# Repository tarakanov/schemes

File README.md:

schemes
=======

Just some schemes

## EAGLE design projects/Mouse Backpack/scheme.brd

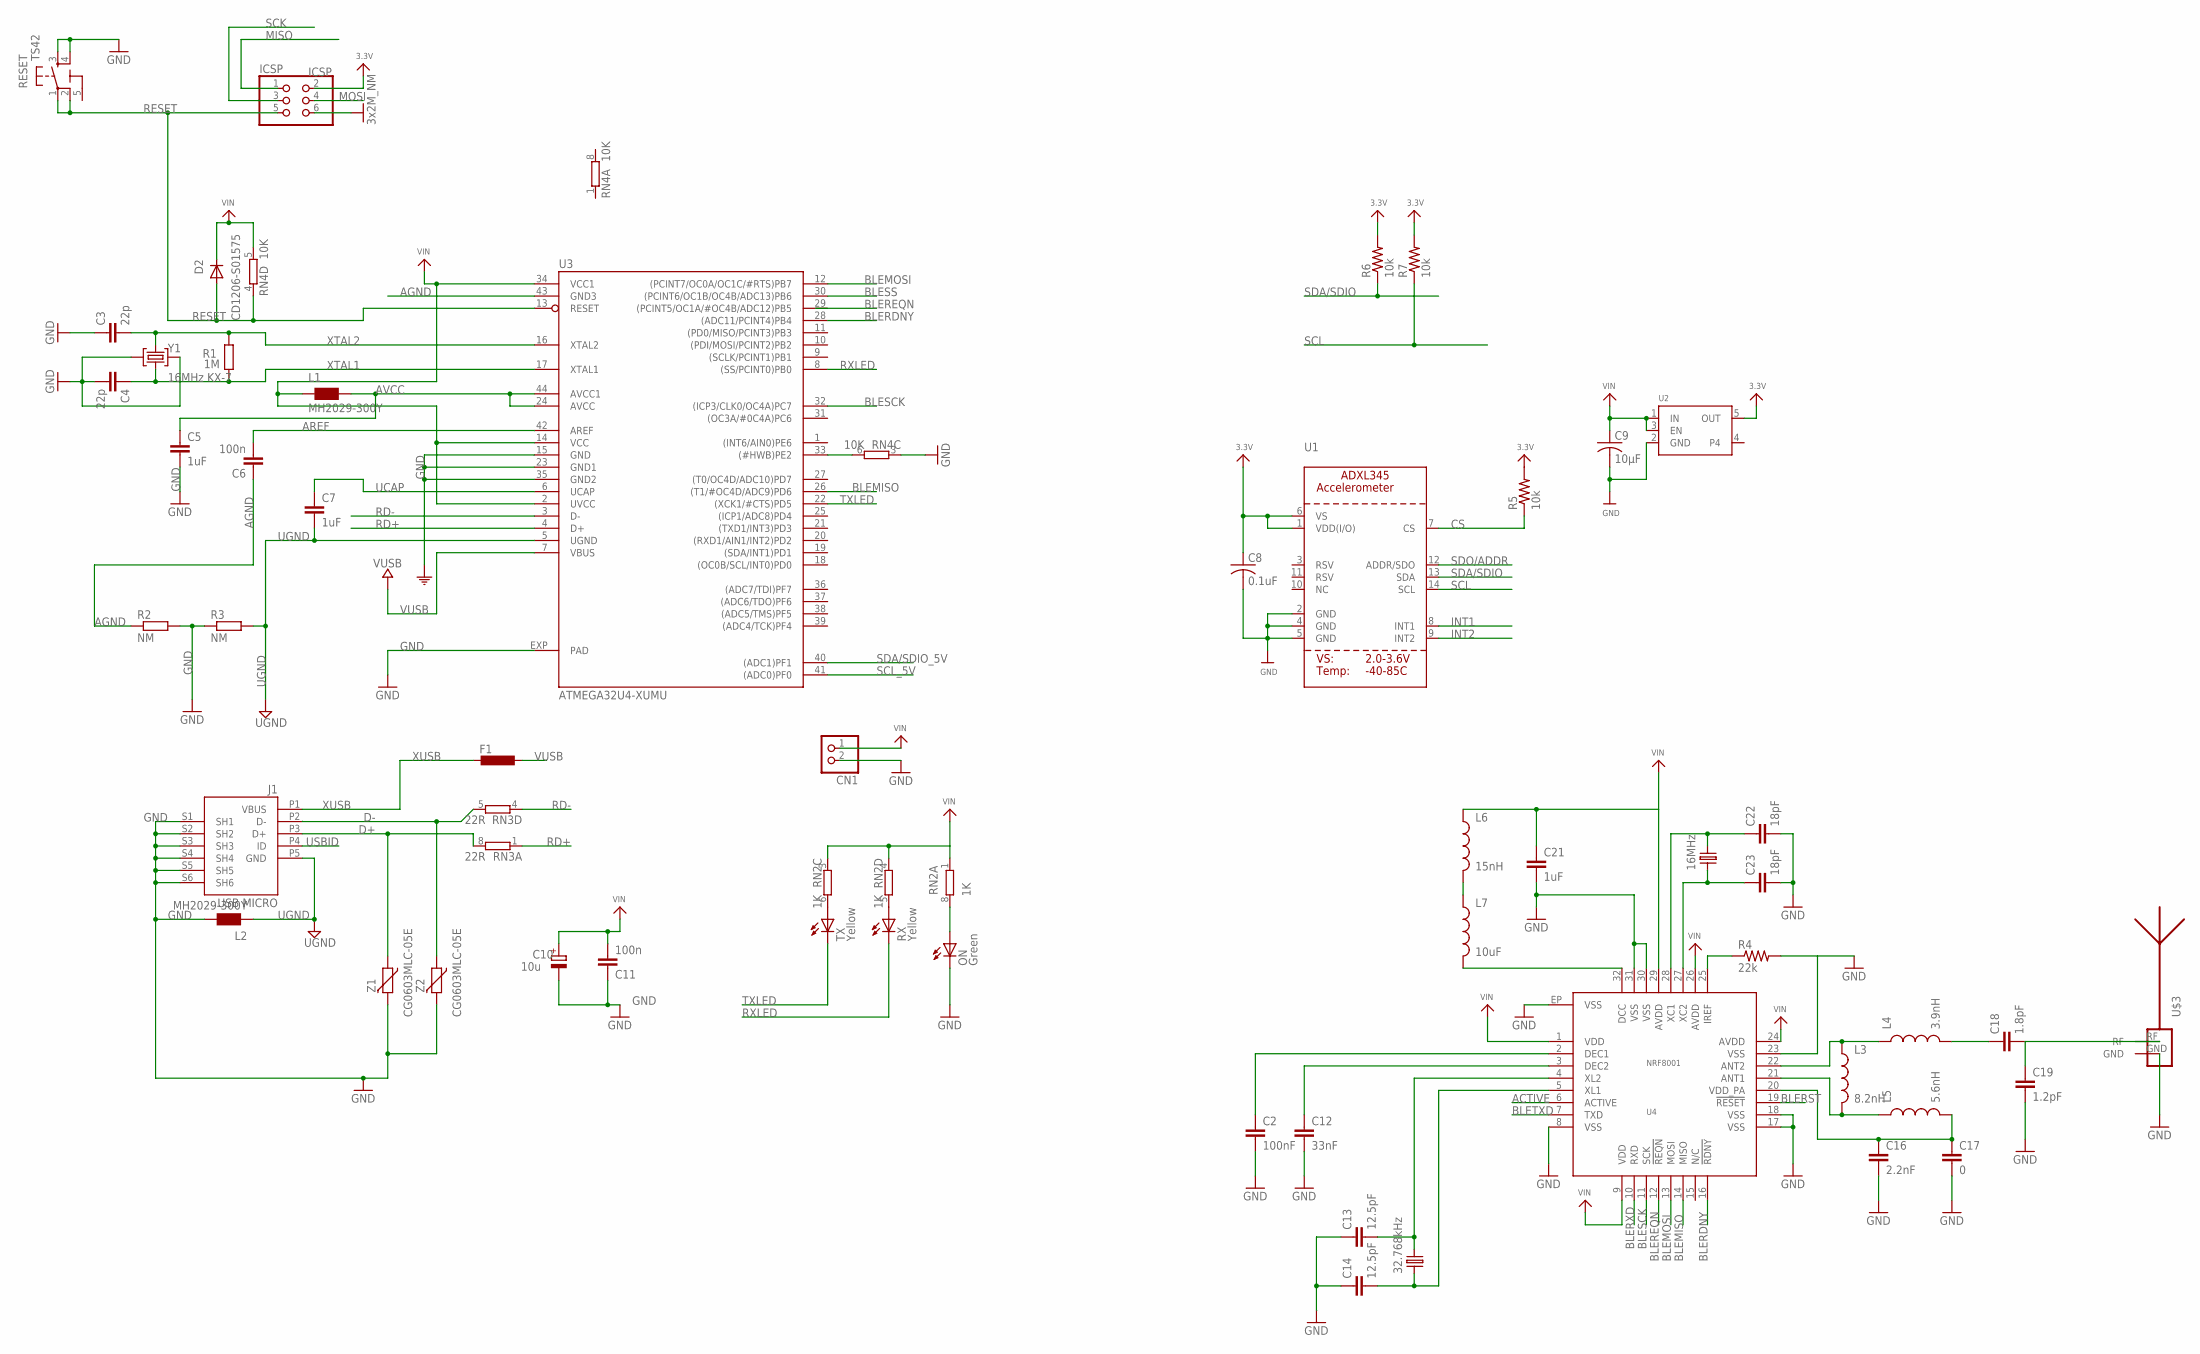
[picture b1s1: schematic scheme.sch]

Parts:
C2: 100nF; 0603-CAP
C3, C4: 22p; C0603-ROUND
C5, C7: 1uF; C0603-ROUND
C6, C11: 100n; C0603-ROUND
C8: 0.1uF; C0805
C9: 10µF; C0805
C10: 10u; SMC_B
C12: 33nF; 0603-CAP
C13, C14: 12.5pF; 0603-CAP
C16: 2.2nF; 0603-CAP
C17: 0; 0603-CAP
C18: 1.8pF; 0603-CAP
C19: 1.2pF; 0603-CAP
C21: 1uF; 0603-CAP
C22, C23: 18pF; 0603-CAP
CN1: JST_2PIN-SMT-RA; JST-PH-2-SMT-RA
D2: CD1206-S01575; MINIMELF
F1: MF-MSMF050-2 500mA; L1812
ICSP: ICSP; 2X03
J1: USB MICRO; CON2_USB_MICRO_B_AT
L1, L2: MH2029-300Y; 0805
L3: 8.2nH; 0603
L4: 3.9nH; 0603
L5: 5.6nH; 0603
L6: 15nH; 0603
L7: 10uF; 0603
ON: Green; CHIPLED_0805
R1: 1M; R0603-ROUND
R2, R3: NM; R0402
R4: 22k; 0603-RES
R5, R6, R7: 10k; 0603-RES
RESET: TS42
RN2: 1K; CAY16
RN3: 22R; CAY16
RN4: 10K; CAY16
RX: Yellow; CHIPLED_0805
TX: Yellow; CHIPLED_0805
U1: ACCEL_ADXL345; LGA14
U2: VREG_SOT23-5; SOT23-5
U3: ATMEGA32U4-XUMU; QFN44ML7X7
U4: NRF8001; QFN-32
U$3: ANTENNA_1LEFT; SWRA117D_LEFT
X1: 16MHz; CRYSTAL-2.5X3.5
X2: 32.768kHz; CRYSTAL-ABS10
Y1: 16MHz KX-7; CRYSTAL-3.2-2.5
Z1, Z2: CG0603MLC-05E; CT/CN0603

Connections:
3.3V: C8.1, ICSP.2, R5.2, R6.2, R7.2, U1.1 (VDD(I/O)), U1.6 (VS), U2.5 (OUT)
5-GND: RESET.5 (5-GND)
ACTIVE: U4.6 (ACTIVE)
AGND: C6.1, R2.1, U3.43 (GND3)
AREF: C6.2, U3.42 (AREF)
AVCC: C5.1, L1.2, U3.24 (AVCC), U3.44 (AVCC1)
BLEMISO: U3.26 ((T1/#OC4D/ADC9)PD6), U4.14 (MISO)
BLEMOSI: U3.12 ((PCINT7/OC0A/OC1C/#RTS)PB7), U4.13 (MOSI)
BLERDNY: U3.28 ((ADC11/PCINT4)PB4), U4.16 (!RDNY)
BLEREQN: U4.12 (!REQN)
BLERST: U4.19 (!RESET)
BLERXD: U4.10 (RXD)
BLESCK: U3.32 ((ICP3/CLK0/OC4A)PC7), U4.11 (SCK)
BLESS: U3.30 ((PCINT6/OC1B/OC4B/ADC13)PB6)
BLETXD: U4.7 (TXD)
CS: R5.1, U1.7 (CS)
D+: J1.P3 (D+), RN3.8 (2), Z1.1
D-: J1.P2 (D-), RN3.5 (2), Z2.1
GND: C2.2, C3.1, C4.2, C5.2, C8.2, C9.2, C10.-, C11.1, C12.2, C13.1, C14.1, C16.2, C17.2, C19.2, C21.2, C22.2, C23.2, CN1.2 (1), ICSP.6, J1.S1 (SH1), J1.S2 (SH2), J1.S3 (SH3), J1.S4 (SH4), J1.S5 (SH5), J1.S6 (SH6), L2.2, ON.C, R2.2, R3.1, R4.2, RESET.3, RESET.4, RN4.3 (1), U1.2 (GND), U1.4 (GND), U1.5 (GND), U2.2 (GND), U3.15 (GND), U3.23 (GND1), U3.35 (GND2), U3.EXP (PAD), U4.8 (VSS), U4.17 (VSS), U4.18 (VSS), U4.23 (VSS), U4.30 (VSS), U4.31 (VSS), U4.EP (VSS), U$3.GND, Y1.2 (GND), Y1.4 (GND), Z1.2, Z2.2
HWB: RN4.6 (2)
INT1: U1.8 (INT1)
INT2: U1.9 (INT2)
MISO: ICSP.1
MOSI: ICSP.4
unnamed: L6.2, L7.1
unnamed: L7.2, U4.32 (DCC)
unnamed: ON.A, RN2.8 (2)
unnamed: C2.1, U4.2 (DEC1)
unnamed: RN2.6 (2), TX.A
unnamed: C12.1, U4.3 (DEC2)
unnamed: RN2.5 (2), RX.A
unnamed: L3.1, L4.1, U4.22 (ANT2)
unnamed: L3.2, L5.1, U4.21 (ANT1)
unnamed: C18.1, L4.2
unnamed: C18.2, C19.1, U$3.RF
unnamed: C16.1, C17.1, L5.2, U4.20 (VDD_PA)
unnamed: R4.1, U4.25 (IREF)
unnamed: C23.1, U4.27 (XC2), X1.P$1
unnamed: C22.1, U4.28 (XC1), X1.P$3
unnamed: C13.2, U4.4 (XL2), X2.P$2
unnamed: C14.2, U4.5 (XL1), X2.P$1
RD+: RN3.1, U3.4 (D+)
RD-: RN3.4 (1), U3.3 (D-)
RESET: D2.A, ICSP.5, RESET.1, RESET.2, RN4.4 (1), U3.13 (RESET)
RXLED: RX.C, U3.8 ((SS/PCINT0)PB0)
SCK: ICSP.3
SCL: R7.1, U1.14 (SCL)
SCL_5V: U3.41 ((ADC0)PF0)
SDA/SDIO: R6.1, U1.13 (SDA)
SDA/SDIO_5V: U3.40 ((ADC1)PF1)
SDO/ADDR: U1.12 (ADDR/SDO)
TXLED: TX.C, U3.22 ((XCK1/#CTS)PD5)
UCAP: C7.1, U3.6 (UCAP)
UGND: C7.2, J1.P5 (GND), L2.1, R3.2, U3.5 (UGND)
USBID: J1.P4 (ID)
VIN: C9.1, C10.+, C11.2, C21.1, CN1.1 (2), D2.C, L1.1, L6.1, RN2.1, RN2.3 (1), RN2.4 (1), RN4.5 (2), U2.1 (IN), U2.3 (EN), U3.2 (UVCC), U3.14 (VCC), U3.34 (VCC1), U4.1 (VDD), U4.9 (VDD), U4.24 (AVDD), U4.26 (AVDD), U4.29 (AVDD)
VUSB: F1.1, U3.7 (VBUS)
XTAL1: C4.1, R1.1, U3.17 (XTAL1), Y1.1 (C1)
XTAL2: C3.2, R1.2, U3.16 (XTAL2), Y1.3 (C2)
XUSB: F1.2, J1.P1 (VBUS)

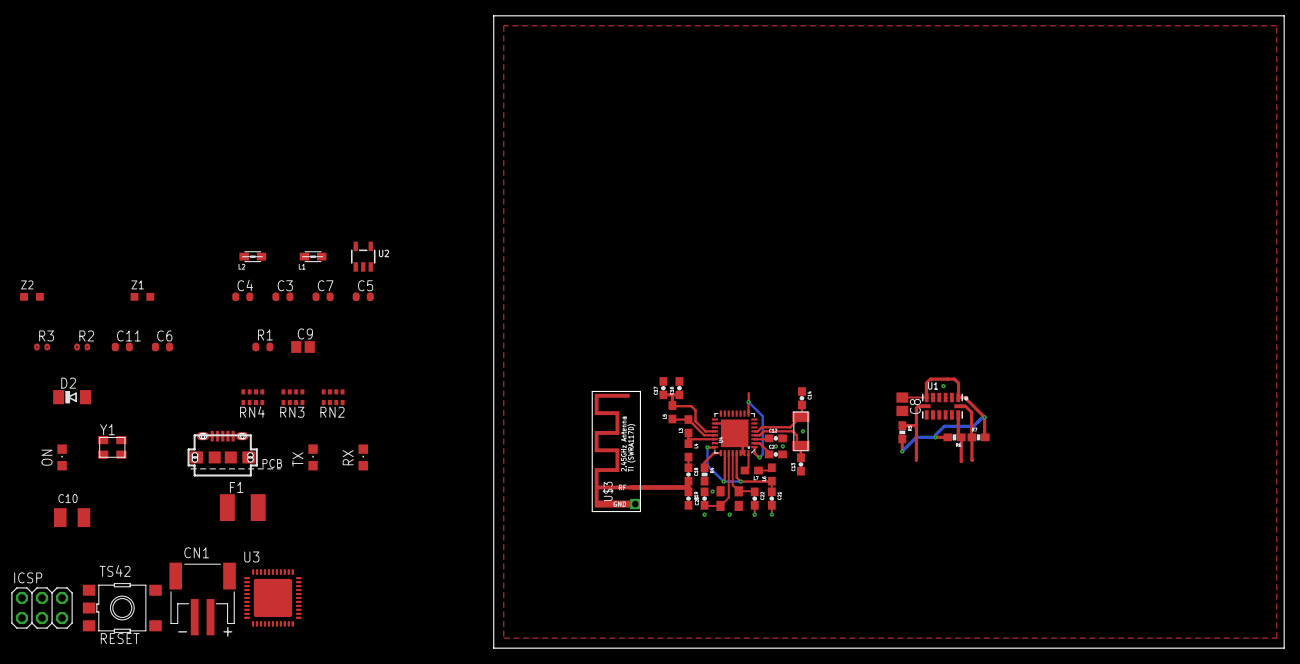
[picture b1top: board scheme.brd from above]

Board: 2 copper layers, 100.0 x 80.0 mm, 56 parts (0 on the bottom side), 43 nets.

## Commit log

2014-03-15 Lots of lbrs
2014-03-15 Mouse backpack
2014-03-15 Gauss gun
2014-03-15 Added 5v supply
2014-03-16 Разводка nRF и ADXL345
    Разводка nRF и ADXL345, небольшие изменения в принципиальной схеме
    adxl345

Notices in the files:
parts and their libraries:
SparkFun: Licensing: CC v3.0 Share-Alike You are welcome to use this library for commercial purposes.
